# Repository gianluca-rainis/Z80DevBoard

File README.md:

# Z80DevBoard

The Z80DevBoard is an advanced development board for the Z80 microprocessor, based on the RP2040.

This board is meant to be a practical educational tool, to help students learn how the Z80, one of the first CPUs and the foundation of all modern ones, works, and how to develop software for it.

To the Z80 is combined a modern RP2040, a powerful microcontroller designed by Raspberry Pi.
It allows easy interaction with the board's components: you can load a program for the Z80 into RAM; or establish a serial connection with the computer to perform live operations, such as reading and writing to RAM.

The most educational components of the board are the LED matrices, which provide real-time visual feedback on the Z80's activity.
Thanks to these LEDs, you can see which address of the RAM the Z80 is accessing, the byte it's reading or writing, whether it is answering to a BUSREQ with a BUSACK, and essentially all the operations the Z80 is executing.

The board mounts five buttons: the four on the right allow the student to save a Z80 program to flash, load a custom firmware for the RP2040, reset the Z80, and put the Z80 into a wait state.
The button on the left sends a manual clock signal to the Z80, in fact, the board mounts a *Z84C00* (the *CMOS* version of the Z80) specifically to allow it to work even with a manual clock.

The board can be connected to a computer through a *USB-C* port, which provides both power and data transmission.
On the bottom-right of the board, are mounted two pin sockets, to support expansion boards or to be used in more advanced projects that require additional hardware.

For more advanced debugging, when testing custom firmware, the *SWD* and *SWCLK* pins of the RP2040 are accessible on the top-right of the board.

---

## Author
The author of the whole project is: 
**Gianluca Rainis** - [gianluca-rainis](https://github.com/gianluca-rainis) on GitHub.

## Sponsor
The PCB prototyping for this project is sponsored by **[PCBWay](https://www.pcbway.com)**.

The *boards* were manufactured with **high precision**, faithfully **following the PCB design down to the smallest details**.
The *silkscreen* is **crisp and perfectly readable**, with **no errors or misalignments**.
The *board edges* and corner's holes were **cut cleanly and accurately**.
The *drill holes* **match the component footprints exactly**, making placement and soldering straightforward.
The *SMD pads* are **precise and clean**, even for the most challenging footprints, and solder beautifully.

The *PCBWay website* is **intuitive, even for first-time users**.
**Placing an order is simple**, and before proceeding to payment **the design is reviewed by their technical staff**, who catch and communicate **any potential manufacturing issues** promptly and professionally, avoiding problems before production even begins.

> If you are looking for a reliable, high-quality PCB manufacturer for your own projects, **[PCBWay](https://www.pcbway.com)** is highly recommended!

## License
### Hardware design files (schematics, PCB, BOM):
Licensed under [CERN-OHL-S v2.0](LICENSE-CERN-OHL-S.md)

### Software, firmware and documentation:
Licensed under the [MIT License](LICENSE-MIT.md)

## AI Disclaimer
**No AI was used in the conception, design, engineering, or development of this project**.
Every circuit and every design decision is the original work of the author.

*AI tools* were used solely as a **writing assistant** for **parts of the documentation**, to help refine and organize technical explanations.
**All content has been reviewed, verified, and edited by the author.**

## Documentation
The full documentation is available in the [`docs/`](docs/index.md) folder.

## Development Tools
- **PCB Design:** KiCad
- **Documentation and code:** Visual Studio Code

## PCB Manufacturing
The Gerber files for PCB manufacturing are available in the [`gerber/`](gerber/) directory.

## Project Structure
```
Z80DevBoard/
├── customFootprints.pretty/  # Custom footprints
├── docs/                     # The documentation and the guides
├── firmware/                 # The RP2040 firmware
├── gerber/                   # PCB manufacturing files (Gerber format)
├── images/                   # Documentation images and KiCad symbols
├── .gitattributes            # Gitattributes file
├── .gitignore                # Gitignore file
├── gerber.zip                # Zip folder with all the gerber files
├── Z80DevBoard.kicad_pcb     # PCB layout file
├── Z80DevBoard.kicad_pro     # KiCad project file
├── Z80DevBoard.kicad_sch     # Schematic file
├── Z80DevBoard.step          # 3D model
├── BOM.csv                   # Bill Of Materials
├── CHANGELOG.md              # Change log of the project
├── JOURNAL.md                # Journal of the project
├── LICENSE-CERN-OHL-S.md     # CERN-OHL-S License
├── LICENSE-MIT.md            # MIT License
└── README.md                 # This file
```

## Images
### Schematic Diagrams
#### Complete Schematic (A2 format)

#### Z80 Section

#### RP2040 Section

### PCB Layout
#### Without Silkscreen

#### With Silkscreen

### 3D Renders
#### Front View

#### Back View

## Technical Details
- **Size**: 219mm x 108.5mm
- **Layers**: 4
- **Supply Voltage**: 5V, 3v3

## Components Table
|Name|Quantity|Class|Type|
|--|--|--|--|
|Z84C00|1|Microprocessor|Through Holes|
|RP2040|1|Microprocessor|SMD|
|||||
|HM62256BLP|2|Memory|Through Holes|
|W25Q32JVSS|1|Memory|SMD|
|||||
|AMS1117-3.3|1|Power Management|SMD|
|||||
|USB C 2.0 port|1|Data Bus|Through Holes|
|74HC595|3|Data Bus|Through Holes|
|74HC155|1|Data Bus|Through Holes|
|74HCT574|4|Data Bus|Through Holes|
|SN74LVC245APW|3|Data Bus|SMD|
|TXS0104EPW|1|Data Bus|SMD|
|Connector 2 pins|1|Data Bus|Through Holes|
|Connector 2×20 pins|1|Data Bus|Through Holes|
|Connector 2×10 pins|1|Data Bus|Through Holes|
|||||
|Crystal 12MHz 20pF|1|Clock|Through Holes|
|Oscillator 8MHz|1|Clock|SMD|
|||||
|74HC14|1|Support components|Through Holes|
|74HC04|1|Support components|Through Holes|
|74HC00|1|Support components|Through Holes|
|||||
|Resistor 0 ohm|1|Resistor|Through Holes|
|Resistor 27.4 ohm|2|Resistor|Through Holes|
|Resistor 1k ohm|36|Resistor|Through Holes|
|Resistor 3.3k ohm|6|Resistor|Through Holes|
|Resistor 5k ohm|2|Resistor|Through Holes|
|Resistor 10k ohm|13|Resistor|Through Holes|
|Resistor 470k ohm|1|Resistor|Through Holes|
|||||
|Capacitors 15pF|2|Capacitor|Through Holes|
|Capacitors 0.1uF|13|Capacitor|Through Holes|
|Capacitors 1uF|4|Capacitor|Through Holes|
|Capacitors 10uF|2|Capacitor|Through Holes|
|||||
|Button|5|Other|Through Holes|
|Switch|1|Other|Through Holes|
|LED|40|Other|SMD|
|Diodes|24|Other|SMD|
|Fuse 500mA|1|Other|SMD|

## Firmware
### Firmware Video Presentation
https://github.com/user-attachments/assets/ee6d8d69-4003-4e21-8f2b-2f08ad0c8d81

### Build
From the project root, make sure CMake and the ARM GNU toolchain (arm-none-eabi-gcc) are installed.

If the toolchain is not in your PATH, provide it explicitly with PICO_TOOLCHAIN_PATH:

```bash
cmake -S firmware -B firmware/build -DPICO_TOOLCHAIN_PATH=/path/to/arm-gnu-toolchain
cmake --build firmware/build --parallel
```

If the toolchain is already in your PATH, you can omit PICO_TOOLCHAIN_PATH.

#### Output file
The file to load in the RP2040's memory after the build is `Z80DevBoard.uf2`.
You can find it in the `/firmware/build` folder.

> You can find more informations about the firmware, including how to write a custom one, in the [documentation](docs/index.md).

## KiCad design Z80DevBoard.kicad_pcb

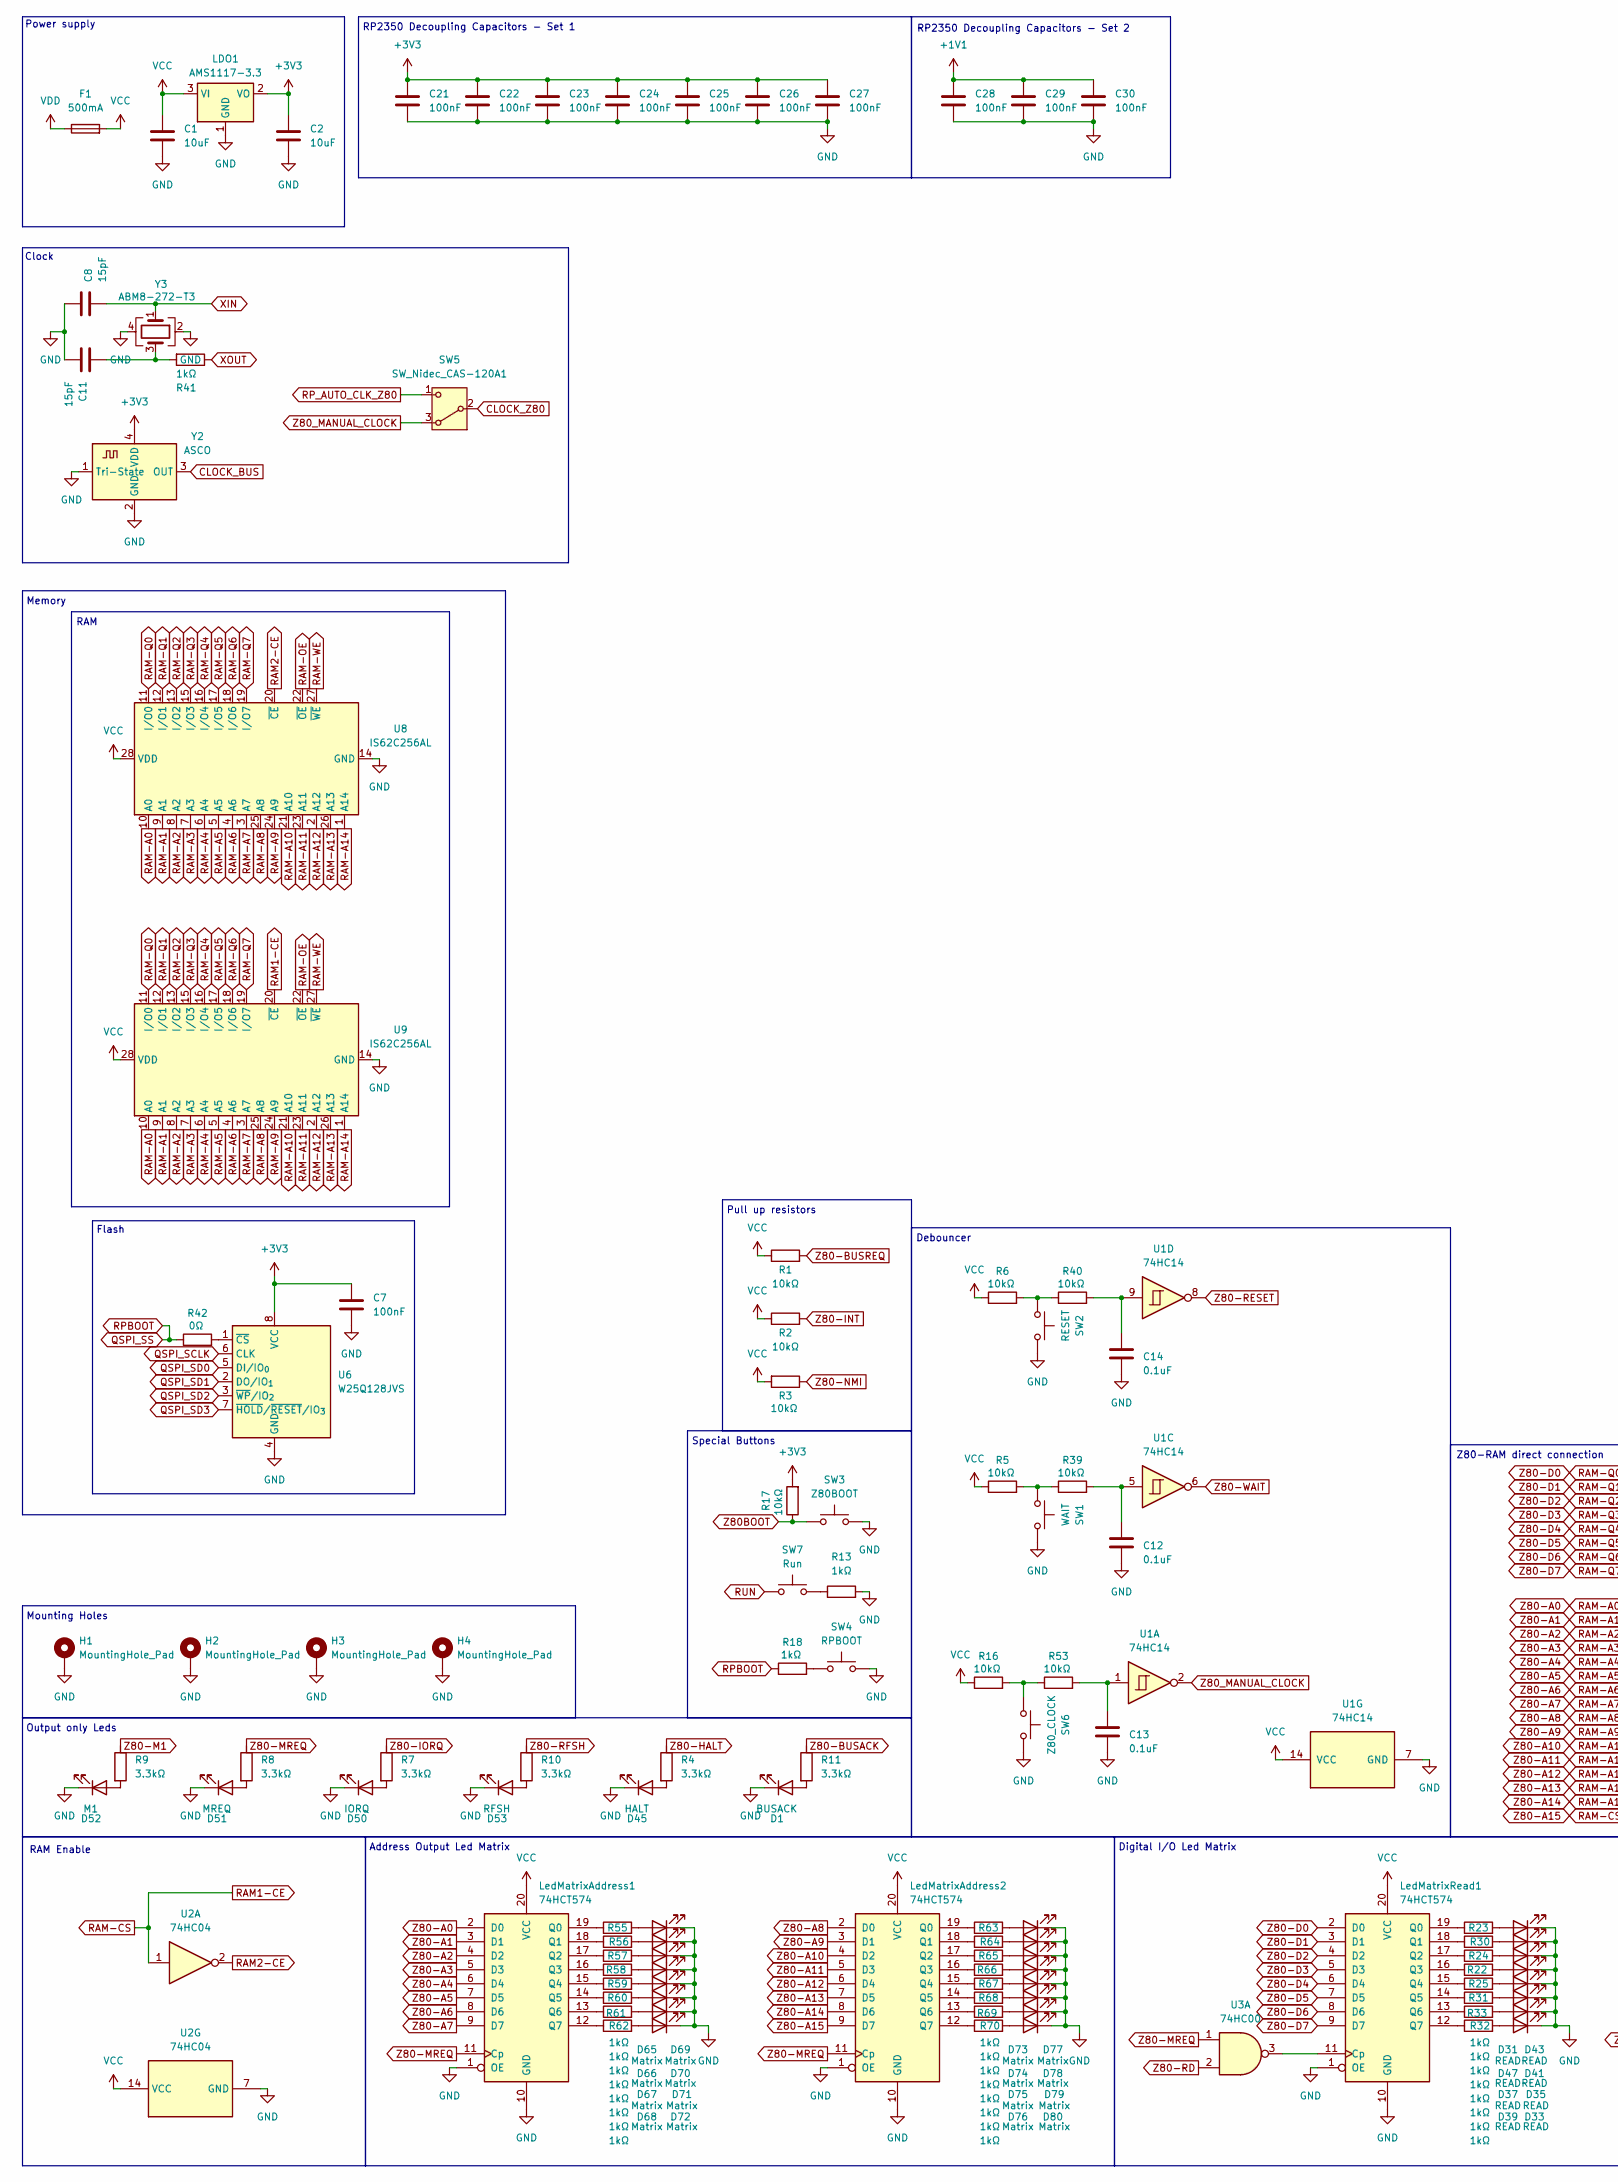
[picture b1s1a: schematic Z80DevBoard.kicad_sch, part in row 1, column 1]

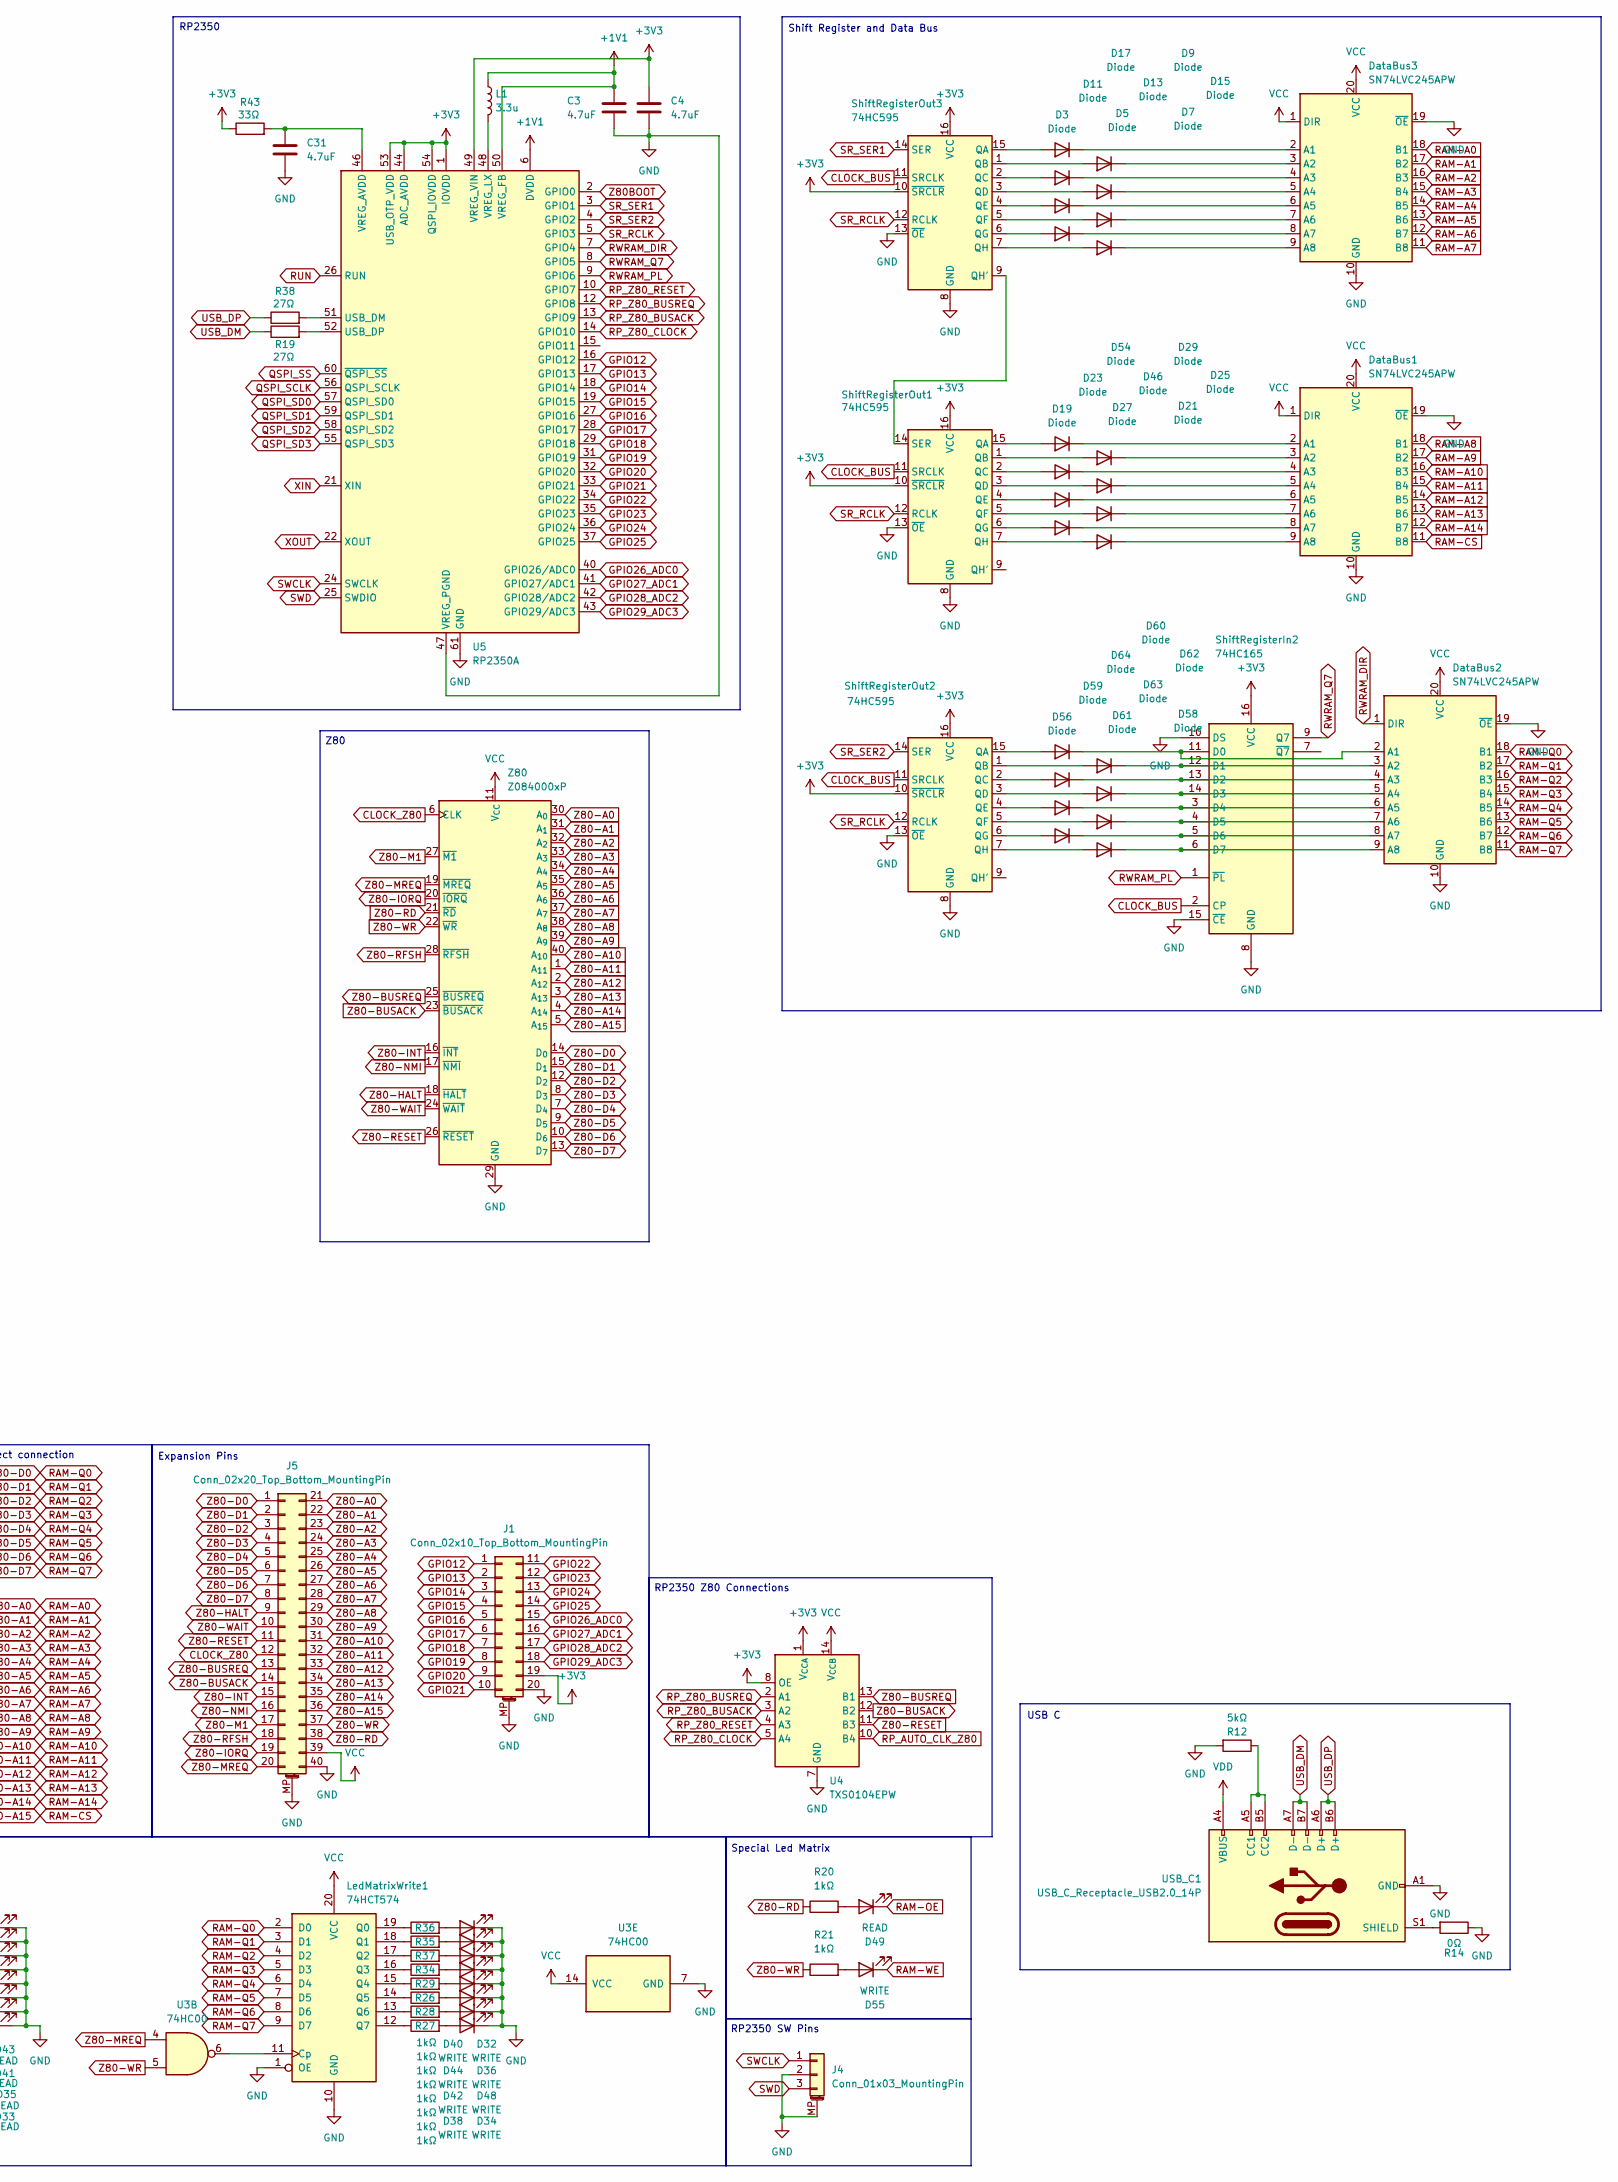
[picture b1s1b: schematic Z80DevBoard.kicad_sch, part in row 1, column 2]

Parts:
C1, C2: 10uF; C_0402_1005Metric
C3, C4, C31: 4.7uF; C_0402_1005Metric
C7, C21, C22, C23, C24, C25, C26, C27, C28, C29, C30: 100nF; C_0402_1005Metric
C8, C11: 15pF; C_0402_1005Metric
C12, C13, C14: 0.1uF; C_0402_1005Metric
D1: BUSACK; LED_PLCC_2835
D3, D5, D7, D9, D11, D13, D15, D17, D19, D21, D23, D25, D27, D29, D46, D54, D56, D58, D59, D60, D61, D62, D63, D64: Diode; D_SOD-523
D31, D33, D35, D37, D39, D41, D43, D47, D49: READ; LED_PLCC_2835
D32, D34, D36, D38, D40, D42, D44, D48, D55: WRITE; LED_PLCC_2835
D45: HALT; LED_PLCC_2835
D50: IORQ; LED_PLCC_2835
D51: MREQ; LED_PLCC_2835
D52: M1; LED_PLCC_2835
D53: RFSH; LED_PLCC_2835
D65, D66, D67, D68, D69, D70, D71, D72, D73, D74, D75, D76, D77, D78, D79, D80: Matrix; LED_PLCC_2835
DataBus1, DataBus2, DataBus3: SN74LVC245APW; TSSOP-20_4.4x6.5mm_P0.65mm
F1: 500mA; Fuse_1206_3216Metric
H1, H2, H3, H4: MountingHole_Pad; MountingHole_4.3mm_M4_Pad_Via
J1: Conn_02x10_Top_Bottom_MountingPin; PinHeader_2x10_P2.54mm_Vertical
J4: Conn_01x03_MountingPin; PinHeader_1x03_P2.54mm_Vertical
J5: Conn_02x20_Top_Bottom_MountingPin; PinHeader_2x20_P2.54mm_Vertical
L1: 3.3u; Inductor
LDO1: AMS1117-3.3; SOT-223-3_TabPin2
LedMatrixAddress1, LedMatrixAddress2: 74HCT574; SO-20_5.3x12.6mm_P1.27mm
LedMatrixRead1: 74HCT574; SO-20_5.3x12.6mm_P1.27mm
LedMatrixWrite1: 74HCT574; SO-20_5.3x12.6mm_P1.27mm
R1, R2, R3, R5, R6, R16, R17, R39, R40, R53: 10kΩ; R_0603_1608Metric
R4, R7, R8, R9, R10, R11: 3.3kΩ; R_0603_1608Metric
R12: 5kΩ; R_0603_1608Metric
R13, R18, R20, R21, R22, R23, R24, R25, R26, R27, R28, R29, R30, R31, R32, R33, R34, R35, R36, R37, R41, R55, R56, R57, R58, R59, R60, R61, R62, R63, R64, R65, R66, R67, R68, R69, R70: 1kΩ; R_0603_1608Metric
R14, R42: 0Ω; R_0603_1608Metric
R19, R38: 27Ω; R_0603_1608Metric
R43: 33Ω; R_0603_1608Metric
SW1: WAIT; SW_SPST_EVQP2_MiddlePushTravel_H2.5mm
SW2: RESET; SW_SPST_EVQP2_MiddlePushTravel_H2.5mm
SW3: Z80BOOT; SW_SPST_EVQP2_MiddlePushTravel_H2.5mm
SW4: RPBOOT; SW_SPST_EVQP2_MiddlePushTravel_H2.5mm
SW5: SW_Nidec_CAS-120A1; SW_Slide-03_Wuerth-WS-SLTV
SW6: Z80_CLOCK; SW_PUSH_6mm_H7.3mm
SW7: Run; SW_SPST_EVQP2_MiddlePushTravel_H2.5mm
ShiftRegisterIn2: 74HC165; SO-16_3.9x9.9mm_P1.27mm
ShiftRegisterOut1, ShiftRegisterOut2, ShiftRegisterOut3: 74HC595; SO-16_3.9x9.9mm_P1.27mm
U1: 74HC14; SO-14_3.9x8.65mm_P1.27mm
U2: 74HC04; SO-14_3.9x8.65mm_P1.27mm
U3: 74HC00; SO-14_3.9x8.65mm_P1.27mm
U4: TXS0104EPW; TSSOP-14_4.4x5mm_P0.65mm
U5: RP2350A; QFN-60-1EP_7x7mm_P0.4mm_EP3.4x3.4mm
U6: W25Q128JVS; SOIC-8_5.3x5.3mm_P1.27mm
U8, U9: IS62C256AL; SOP-28_8.4x18.16mm_P1.27mm
USB_C1: USB_C_Receptacle_USB2.0_14P; USB_C_Receptacle_HRO_TYPE-C-31-M-12
Y2: ASCO; Oscillator_SMD_SiT_PQFN-4Pin_5.0x3.2mm
Y3: ABM8-272-T3; Crystal_SMD_3225-4Pin_3.2x2.5mm; LCSC Part # C20625731
Z80: Z084000xP; DIP-40_W15.24mm

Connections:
+1V1: C3.1, C28.1, C29.1, C30.1, L1.1, U5.6 (DVDD), U5.23 (DVDD), U5.39 (DVDD), U5.50 (VREG_FB)
+3V3: C2.2, C4.1, C7.2, C21.1, C22.1, C23.1, C24.1, C25.1, C26.1, C27.1, J1.19, LDO1.2 (VO), R17.2, R43.1, ShiftRegisterIn2.16 (VCC), ShiftRegisterOut1.10 (~SRCLR), ShiftRegisterOut1.16 (VCC), ShiftRegisterOut2.10 (~SRCLR), ShiftRegisterOut2.16 (VCC), ShiftRegisterOut3.10 (~SRCLR), ShiftRegisterOut3.16 (VCC), U4.1 (V_{CCA}), U4.8 (OE), U5.1 (IOVDD), U5.11 (IOVDD), U5.20 (IOVDD), U5.30 (IOVDD), U5.38 (IOVDD), U5.44 (ADC_AVDD), U5.45 (IOVDD), U5.49 (VREG_VIN), U5.53 (USB_OTP_VDD), U5.54 (QSPI_IOVDD), U6.8 (VCC), Y2.4 (VDD)
CLOCK_BUS: ShiftRegisterIn2.2 (CP), ShiftRegisterOut1.11 (SRCLK), ShiftRegisterOut2.11 (SRCLK), ShiftRegisterOut3.11 (SRCLK), Y2.3 (OUT)
CLOCK_Z80: J5.12, SW5.2 (B), Z80.6 (CLK)
GND: C1.1, C2.1, C3.2, C4.2, C7.1, C8.2, C11.1, C12.1, C13.1, C14.1, C21.2, C22.2, C23.2, C24.2, C25.2, C26.2, C27.2, C28.2, C29.2, C30.2, C31.2, D1.1 (K), D31.1 (K), D32.1 (K), D33.1 (K), D34.1 (K), D35.1 (K), D36.1 (K), D37.1 (K), D38.1 (K), D39.1 (K), D40.1 (K), D41.1 (K), D42.1 (K), D43.1 (K), D44.1 (K), D45.1 (K), D47.1 (K), D48.1 (K), D50.1 (K), D51.1 (K), D52.1 (K), D53.1 (K), D65.1 (K), D66.1 (K), D67.1 (K), D68.1 (K), D69.1 (K), D70.1 (K), D71.1 (K), D72.1 (K), D73.1 (K), D74.1 (K), D75.1 (K), D76.1 (K), D77.1 (K), D78.1 (K), D79.1 (K), D80.1 (K), DataBus1.10 (GND), DataBus1.19 (~OE), DataBus2.10 (GND), DataBus2.19 (~OE), DataBus3.10 (GND), DataBus3.19 (~OE), H1.1 (1_1), H2.1 (1_1), H3.1 (1_1), H4.1 (1_1), J1.20, J1.MP (MountPin), J4.2, J4.MP (MountPin), J5.40, J5.MP (MountPin), LDO1.1 (GND), LedMatrixAddress1.1 (OE), LedMatrixAddress1.10 (GND), LedMatrixAddress2.1 (OE), LedMatrixAddress2.10 (GND), LedMatrixRead1.1 (OE), LedMatrixRead1.10 (GND), LedMatrixWrite1.1 (OE), LedMatrixWrite1.10 (GND), R12.2, R13.2, R14.1, SW1.1, SW2.1, SW3.1, SW4.1, SW6.1, ShiftRegisterIn2.8 (GND), ShiftRegisterIn2.10 (DS), ShiftRegisterIn2.15 (~CE), ShiftRegisterOut1.8 (GND), ShiftRegisterOut1.13 (~OE), ShiftRegisterOut2.8 (GND), ShiftRegisterOut2.13 (~OE), ShiftRegisterOut3.8 (GND), ShiftRegisterOut3.13 (~OE), U1.7 (GND), U2.7 (GND), U3.7 (GND), U4.7 (GND), U5.47 (VREG_PGND), U5.61 (GND), U6.4 (GND), U8.14 (GND), U9.14 (GND), USB_C1.A1 (GND), USB_C1.A12 (GND), USB_C1.B1 (GND), USB_C1.B12 (GND), Y2.1 (Tri-State), Y2.2 (GND), Y3.2, Y3.4, Z80.29 (GND)
GPIO12: J1.1, U5.16 (GPIO12)
GPIO13: J1.2, U5.17 (GPIO13)
GPIO14: J1.3, U5.18 (GPIO14)
GPIO15: J1.4, U5.19 (GPIO15)
GPIO16: J1.5, U5.27 (GPIO16)
GPIO17: J1.6, U5.28 (GPIO17)
GPIO18: J1.7, U5.29 (GPIO18)
GPIO19: J1.8, U5.31 (GPIO19)
GPIO20: J1.9, U5.32 (GPIO20)
GPIO21: J1.10, U5.33 (GPIO21)
GPIO22: J1.11, U5.34 (GPIO22)
GPIO23: J1.12, U5.35 (GPIO23)
GPIO24: J1.13, U5.36 (GPIO24)
GPIO25: J1.14, U5.37 (GPIO25)
GPIO26_ADC0: J1.15, U5.40 (GPIO26/ADC0)
GPIO27_ADC1: J1.16, U5.41 (GPIO27/ADC1)
GPIO28_ADC2: J1.17, U5.42 (GPIO28/ADC2)
GPIO29_ADC3: J1.18, U5.43 (GPIO29/ADC3)
unnamed: C11.2, R41.2, Y3.3
unnamed: C12.2, R39.2, U1.5
unnamed: C13.2, R53.2, U1.1
unnamed: C14.2, R40.2, U1.9
unnamed: D1.2 (A), R11.2
unnamed: D3.2 (A), ShiftRegisterOut3.15 (QA)
unnamed: D3.1 (K), DataBus3.2 (A1)
unnamed: D5.2 (A), ShiftRegisterOut3.1 (QB)
unnamed: D5.1 (K), DataBus3.3 (A2)
unnamed: D7.2 (A), ShiftRegisterOut3.2 (QC)
unnamed: D7.1 (K), DataBus3.4 (A3)
unnamed: D9.2 (A), ShiftRegisterOut3.3 (QD)
unnamed: D9.1 (K), DataBus3.5 (A4)
unnamed: D11.2 (A), ShiftRegisterOut3.4 (QE)
unnamed: D11.1 (K), DataBus3.6 (A5)
unnamed: D13.2 (A), ShiftRegisterOut3.5 (QF)
unnamed: D13.1 (K), DataBus3.7 (A6)
unnamed: D15.2 (A), ShiftRegisterOut3.6 (QG)
unnamed: D15.1 (K), DataBus3.8 (A7)
unnamed: D17.2 (A), ShiftRegisterOut3.7 (QH)
unnamed: D17.1 (K), DataBus3.9 (A8)
unnamed: D19.2 (A), ShiftRegisterOut1.15 (QA)
unnamed: D19.1 (K), DataBus1.2 (A1)
unnamed: D21.2 (A), ShiftRegisterOut1.2 (QC)
unnamed: D21.1 (K), DataBus1.4 (A3)
unnamed: D23.2 (A), ShiftRegisterOut1.4 (QE)
unnamed: D23.1 (K), DataBus1.6 (A5)
unnamed: D25.2 (A), ShiftRegisterOut1.6 (QG)
unnamed: D25.1 (K), DataBus1.8 (A7)
unnamed: D27.2 (A), ShiftRegisterOut1.1 (QB)
unnamed: D27.1 (K), DataBus1.3 (A2)
unnamed: D29.2 (A), ShiftRegisterOut1.3 (QD)
unnamed: D29.1 (K), DataBus1.5 (A4)
unnamed: D31.2 (A), R23.2
unnamed: D32.2 (A), R29.2
unnamed: D33.2 (A), R32.2
unnamed: D34.2 (A), R27.2
unnamed: D35.2 (A), R33.2
unnamed: D36.2 (A), R26.2
unnamed: D37.2 (A), R24.2
unnamed: D38.2 (A), R34.2
unnamed: D39.2 (A), R22.2
unnamed: D40.2 (A), R36.2
unnamed: D41.2 (A), R31.2
unnamed: D42.2 (A), R37.2
unnamed: D43.2 (A), R25.2
unnamed: D44.2 (A), R35.2
unnamed: D45.2 (A), R4.2
unnamed: D46.2 (A), ShiftRegisterOut1.5 (QF)
unnamed: D46.1 (K), DataBus1.7 (A6)
unnamed: D47.2 (A), R30.2
unnamed: D48.2 (A), R28.2
unnamed: D49.2 (A), R20.2
unnamed: D50.2 (A), R7.2
unnamed: D51.2 (A), R8.2
unnamed: D52.2 (A), R9.2
unnamed: D53.2 (A), R10.2
unnamed: D54.2 (A), ShiftRegisterOut1.7 (QH)
unnamed: D54.1 (K), DataBus1.9 (A8)
unnamed: D55.2 (A), R21.2
unnamed: D56.2 (A), ShiftRegisterOut2.15 (QA)
unnamed: D56.1 (K), DataBus2.2 (A1), ShiftRegisterIn2.11 (D0)
unnamed: D58.2 (A), ShiftRegisterOut2.2 (QC)
unnamed: D58.1 (K), DataBus2.4 (A3), ShiftRegisterIn2.13 (D2)
unnamed: D59.2 (A), ShiftRegisterOut2.4 (QE)
unnamed: D59.1 (K), DataBus2.6 (A5), ShiftRegisterIn2.3 (D4)
unnamed: D60.2 (A), ShiftRegisterOut2.6 (QG)
unnamed: D60.1 (K), DataBus2.8 (A7), ShiftRegisterIn2.5 (D6)
unnamed: D61.2 (A), ShiftRegisterOut2.1 (QB)
unnamed: D61.1 (K), DataBus2.3 (A2), ShiftRegisterIn2.12 (D1)
unnamed: D62.2 (A), ShiftRegisterOut2.3 (QD)
unnamed: D62.1 (K), DataBus2.5 (A4), ShiftRegisterIn2.14 (D3)
unnamed: D63.2 (A), ShiftRegisterOut2.5 (QF)
unnamed: D63.1 (K), DataBus2.7 (A6), ShiftRegisterIn2.4 (D5)
unnamed: D64.2 (A), ShiftRegisterOut2.7 (QH)
unnamed: D64.1 (K), DataBus2.9 (A8), ShiftRegisterIn2.6 (D7)
unnamed: D65.2 (A), R55.2
unnamed: D66.2 (A), R56.2
unnamed: D67.2 (A), R57.2
unnamed: D68.2 (A), R58.2
unnamed: D69.2 (A), R59.2
unnamed: D70.2 (A), R60.2
unnamed: D71.2 (A), R61.2
unnamed: D72.2 (A), R62.2
unnamed: D73.2 (A), R63.2
unnamed: D74.2 (A), R64.2
unnamed: D75.2 (A), R65.2
unnamed: D76.2 (A), R66.2
unnamed: D77.2 (A), R67.2
unnamed: D78.2 (A), R68.2
unnamed: D79.2 (A), R69.2
unnamed: D80.2 (A), R70.2
unnamed: LedMatrixAddress1.19 (Q0), R55.1
unnamed: LedMatrixAddress1.18 (Q1), R56.1
unnamed: LedMatrixAddress1.17 (Q2), R57.1
unnamed: LedMatrixAddress1.16 (Q3), R58.1
unnamed: LedMatrixAddress1.15 (Q4), R59.1
unnamed: LedMatrixAddress1.14 (Q5), R60.1
unnamed: LedMatrixAddress1.13 (Q6), R61.1
unnamed: LedMatrixAddress1.12 (Q7), R62.1
unnamed: LedMatrixAddress2.19 (Q0), R63.1
unnamed: LedMatrixAddress2.18 (Q1), R64.1
unnamed: LedMatrixAddress2.17 (Q2), R65.1
unnamed: LedMatrixAddress2.16 (Q3), R66.1
unnamed: LedMatrixAddress2.15 (Q4), R67.1
unnamed: LedMatrixAddress2.14 (Q5), R68.1
unnamed: LedMatrixAddress2.13 (Q6), R69.1
unnamed: LedMatrixAddress2.12 (Q7), R70.1
unnamed: LedMatrixRead1.11 (Cp), U3.3
unnamed: LedMatrixRead1.19 (Q0), R23.1
unnamed: LedMatrixRead1.18 (Q1), R30.1
unnamed: LedMatrixRead1.17 (Q2), R24.1
unnamed: LedMatrixRead1.16 (Q3), R22.1
unnamed: LedMatrixRead1.15 (Q4), R25.1
unnamed: LedMatrixRead1.14 (Q5), R31.1
unnamed: LedMatrixRead1.13 (Q6), R33.1
unnamed: LedMatrixRead1.12 (Q7), R32.1
unnamed: LedMatrixWrite1.11 (Cp), U3.6
unnamed: LedMatrixWrite1.19 (Q0), R36.1
unnamed: LedMatrixWrite1.18 (Q1), R35.1
unnamed: LedMatrixWrite1.17 (Q2), R37.1
unnamed: LedMatrixWrite1.16 (Q3), R34.1
unnamed: LedMatrixWrite1.15 (Q4), R29.1
unnamed: LedMatrixWrite1.14 (Q5), R26.1
unnamed: LedMatrixWrite1.13 (Q6), R28.1
unnamed: LedMatrixWrite1.12 (Q7), R27.1
unnamed: R13.1, SW7.2
unnamed: R16.2, R53.1, SW6.2
unnamed: R18.2, SW4.2
unnamed: R5.2, R39.1, SW1.2
unnamed: R6.2, R40.1, SW2.2
unnamed: ShiftRegisterOut1.14 (SER), ShiftRegisterOut3.9 (QH')
unnamed: R38.2, U5.51 (USB_DM)
unnamed: R19.2, U5.52 (USB_DP)
unnamed: C31.1, R43.2, U5.46 (VREG_AVDD)
unnamed: L1.2, U5.48 (VREG_LX)
unnamed: R42.2, U6.1 (~CS)
unnamed: R12.1, USB_C1.A5 (CC1), USB_C1.B5 (CC2)
unnamed: R14.2, USB_C1.S1 (SHIELD)
QSPI_SCLK: U5.56 (QSPI_SCLK), U6.6 (CLK)
QSPI_SD0: U5.57 (QSPI_SD0), U6.5 (DI/IO_{0})
QSPI_SD1: U5.59 (QSPI_SD1), U6.2 (DO/IO_{1})
QSPI_SD2: U5.58 (QSPI_SD2), U6.3 (~WP/IO_{2})
QSPI_SD3: U5.55 (QSPI_SD3), U6.7 (~HOLD/~RESET/IO_{3})
QSPI_SS: R18.1, R42.1, U5.60 (~QSPI_SS)
RAM2-CE: U2.2, U8.20 (~CE)
RAM-A0: DataBus3.18 (B1), J5.21, LedMatrixAddress1.2 (D0), U8.10 (A0), U9.10 (A0), Z80.30 (A_{0})
RAM-A1: DataBus3.17 (B2), J5.22, LedMatrixAddress1.3 (D1), U8.9 (A1), U9.9 (A1), Z80.31 (A_{1})
RAM-A2: DataBus3.16 (B3), J5.23, LedMatrixAddress1.4 (D2), U8.8 (A2), U9.8 (A2), Z80.32 (A_{2})
RAM-A3: DataBus3.15 (B4), J5.24, LedMatrixAddress1.5 (D3), U8.7 (A3), U9.7 (A3), Z80.33 (A_{3})
RAM-A4: DataBus3.14 (B5), J5.25, LedMatrixAddress1.6 (D4), U8.6 (A4), U9.6 (A4), Z80.34 (A_{4})
RAM-A5: DataBus3.13 (B6), J5.26, LedMatrixAddress1.7 (D5), U8.5 (A5), U9.5 (A5), Z80.35 (A_{5})
RAM-A6: DataBus3.12 (B7), J5.27, LedMatrixAddress1.8 (D6), U8.4 (A6), U9.4 (A6), Z80.36 (A_{6})
RAM-A7: DataBus3.11 (B8), J5.28, LedMatrixAddress1.9 (D7), U8.3 (A7), U9.3 (A7), Z80.37 (A_{7})
RAM-A8: DataBus1.18 (B1), J5.29, LedMatrixAddress2.2 (D0), U8.25 (A8), U9.25 (A8), Z80.38 (A_{8})
RAM-A9: DataBus1.17 (B2), J5.30, LedMatrixAddress2.3 (D1), U8.24 (A9), U9.24 (A9), Z80.39 (A_{9})
RAM-A10: DataBus1.16 (B3), J5.31, LedMatrixAddress2.4 (D2), U8.21 (A10), U9.21 (A10), Z80.40 (A_{10})
RAM-A11: DataBus1.15 (B4), J5.32, LedMatrixAddress2.5 (D3), U8.23 (A11), U9.23 (A11), Z80.1 (A_{11})
RAM-A12: DataBus1.14 (B5), J5.33, LedMatrixAddress2.6 (D4), U8.2 (A12), U9.2 (A12), Z80.2 (A_{12})
RAM-A13: DataBus1.13 (B6), J5.34, LedMatrixAddress2.7 (D5), U8.26 (A13), U9.26 (A13), Z80.3 (A_{13})
RAM-A14: DataBus1.12 (B7), J5.35, LedMatrixAddress2.8 (D6), U8.1 (A14), U9.1 (A14), Z80.4 (A_{14})
RAM-CS: DataBus1.11 (B8), J5.36, LedMatrixAddress2.9 (D7), U2.1, U9.20 (~CE), Z80.5 (A_{15})
RAM-OE: D49.1 (K), U8.22 (~OE), U9.22 (~OE)
RAM-Q0: DataBus2.18 (B1), J5.1, LedMatrixRead1.2 (D0), LedMatrixWrite1.2 (D0), U8.11 (I/O0), U9.11 (I/O0), Z80.14 (D_{0})
RAM-Q1: DataBus2.17 (B2), J5.2, LedMatrixRead1.3 (D1), LedMatrixWrite1.3 (D1), U8.12 (I/O1), U9.12 (I/O1), Z80.15 (D_{1})
RAM-Q2: DataBus2.16 (B3), J5.3, LedMatrixRead1.4 (D2), LedMatrixWrite1.4 (D2), U8.13 (I/O2), U9.13 (I/O2), Z80.12 (D_{2})
RAM-Q3: DataBus2.15 (B4), J5.4, LedMatrixRead1.5 (D3), LedMatrixWrite1.5 (D3), U8.15 (I/O3), U9.15 (I/O3), Z80.8 (D_{3})
RAM-Q4: DataBus2.14 (B5), J5.5, LedMatrixRead1.6 (D4), LedMatrixWrite1.6 (D4), U8.16 (I/O4), U9.16 (I/O4), Z80.7 (D_{4})
RAM-Q5: DataBus2.13 (B6), J5.6, LedMatrixRead1.7 (D5), LedMatrixWrite1.7 (D5), U8.17 (I/O5), U9.17 (I/O5), Z80.9 (D_{5})
RAM-Q6: DataBus2.12 (B7), J5.7, LedMatrixRead1.8 (D6), LedMatrixWrite1.8 (D6), U8.18 (I/O6), U9.18 (I/O6), Z80.10 (D_{6})
RAM-Q7: DataBus2.11 (B8), J5.8, LedMatrixRead1.9 (D7), LedMatrixWrite1.9 (D7), U8.19 (I/O7), U9.19 (I/O7), Z80.13 (D_{7})
RAM-WE: D55.1 (K), U8.27 (~WE), U9.27 (~WE)
RP_AUTO_CLK_Z80: SW5.1 (C), U4.10 (B4)
RP_Z80_BUSACK: U4.3 (A2), U5.13 (GPIO9)
RP_Z80_BUSREQ: U4.2 (A1), U5.12 (GPIO8)
RP_Z80_CLOCK: U4.5 (A4), U5.14 (GPIO10)
RP_Z80_RESET: U4.4 (A3), U5.10 (GPIO7)
RUN: SW7.1, U5.26 (RUN)
RWRAM_DIR: DataBus2.1 (DIR), U5.7 (GPIO4)
RWRAM_PL: ShiftRegisterIn2.1 (~PL), U5.9 (GPIO6)
RWRAM_Q7: ShiftRegisterIn2.9 (Q7), U5.8 (GPIO5)
SR_RCLK: ShiftRegisterOut1.12 (RCLK), ShiftRegisterOut2.12 (RCLK), ShiftRegisterOut3.12 (RCLK), U5.5 (GPIO3)
SR_SER1: ShiftRegisterOut3.14 (SER), U5.3 (GPIO1)
SR_SER2: ShiftRegisterOut2.14 (SER), U5.4 (GPIO2)
SWCLK: J4.1, U5.24 (SWCLK)
SWD: J4.3, U5.25 (SWDIO)
USB_DM: R19.1, USB_C1.A7 (D-), USB_C1.B7 (D-)
USB_DP: R38.1, USB_C1.A6 (D+), USB_C1.B6 (D+)
VCC: C1.2, DataBus1.1 (DIR), DataBus1.20 (VCC), DataBus2.20 (VCC), DataBus3.1 (DIR), DataBus3.20 (VCC), F1.2, J5.39, LDO1.3 (VI), LedMatrixAddress1.20 (VCC), LedMatrixAddress2.20 (VCC), LedMatrixRead1.20 (VCC), LedMatrixWrite1.20 (VCC), R1.1, R2.1, R3.2, R5.1, R6.1, R16.1, U1.14 (VCC), U2.14 (VCC), U3.14 (VCC), U4.14 (V_{CCB}), U8.28 (VDD), U9.28 (VDD), Z80.11 (V_{CC})
VDD: F1.1, USB_C1.A4 (VBUS), USB_C1.A9 (VBUS), USB_C1.B4 (VBUS), USB_C1.B9 (VBUS)
XIN: C8.1, U5.21 (XIN), Y3.1
XOUT: R41.1, U5.22 (XOUT)
Z80-BUSACK: J5.14, R11.1, U4.12 (B2), Z80.23 (~BUSACK)
Z80-BUSREQ: J5.13, R1.2, U4.13 (B1), Z80.25 (~BUSREQ)
Z80-HALT: J5.9, R4.1, Z80.18 (~HALT)
Z80-INT: J5.15, R2.2, Z80.16 (~INT)
Z80-IORQ: J5.19, R7.1, Z80.20 (~IORQ)
Z80-M1: J5.17, R9.1, Z80.27 (~M1)
Z80-MREQ: J5.20, LedMatrixAddress1.11 (Cp), LedMatrixAddress2.11 (Cp), R8.1, U3.1, U3.4, Z80.19 (~MREQ)
Z80-NMI: J5.16, R3.1, Z80.17 (~NMI)
Z80-RD: J5.38, R20.1, U3.2, Z80.21 (~RD)
Z80-RESET: J5.11, U1.8, U4.11 (B3), Z80.26 (~RESET)
Z80-RFSH: J5.18, R10.1, Z80.28 (~RFSH)
Z80-WAIT: J5.10, U1.6, Z80.24 (~WAIT)
Z80-WR: J5.37, R21.1, U3.5, Z80.22 (~WR)
Z80BOOT: R17.1, SW3.2, U5.2 (GPIO0)
Z80_MANUAL_CLOCK: SW5.3 (A), U1.2

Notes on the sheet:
Digital I/O Led Matrix
RAM
Special Buttons
Power supply
RP2350 Z80 Connections
Debouncer
Expansion Pins
Z80
Mounting Holes
Output only Leds
Clock
USB C
Address Output Led Matrix
RP2350 Decoupling Capacitors - Set 1
RP2350 SW Pins
Z80-RAM direct connection
RP2350
Special Led Matrix
Pull up resistors
Shift Register and Data Bus
Memory
Flash
RAM Enable
RP2350 Decoupling Capacitors - Set 2

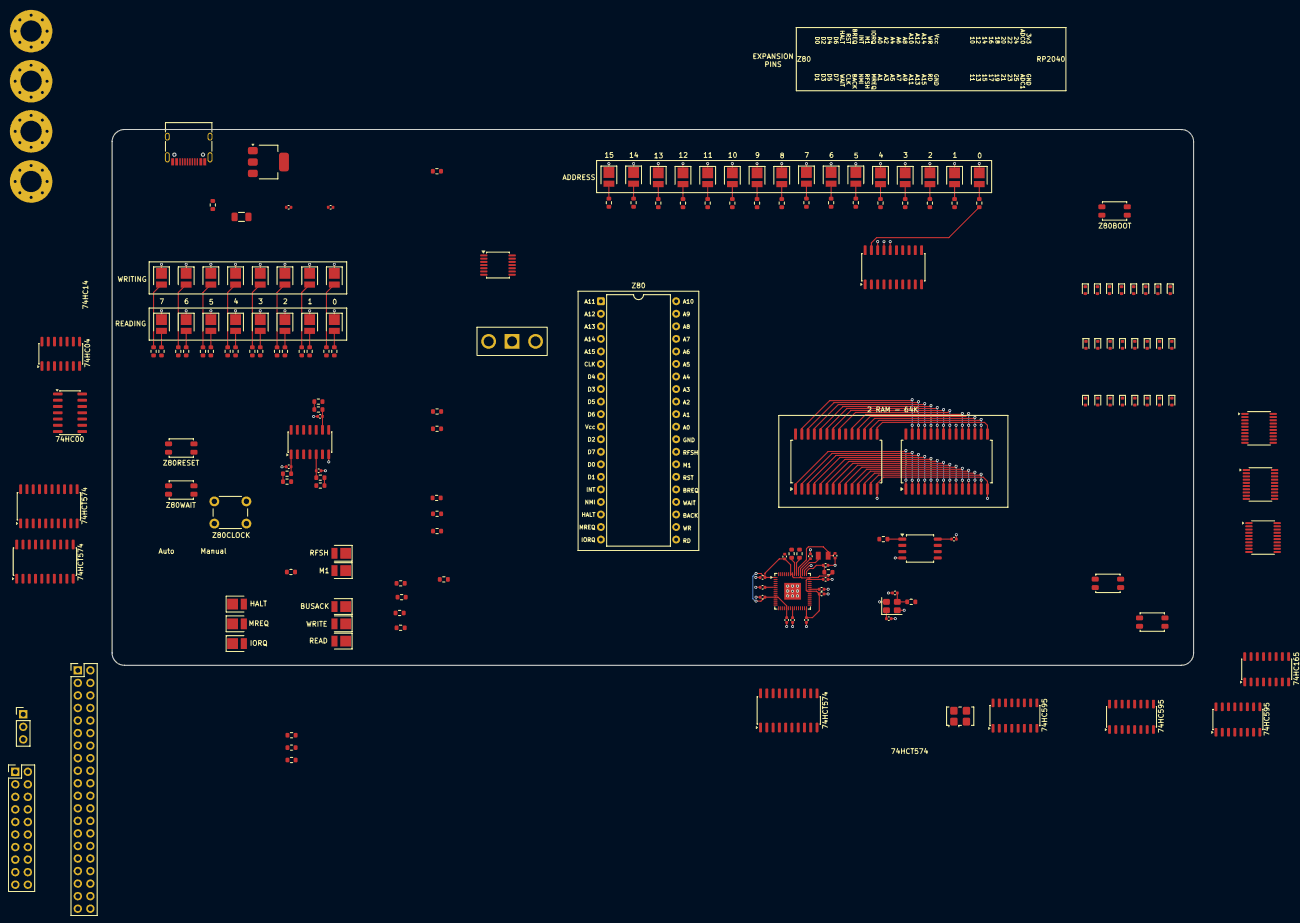
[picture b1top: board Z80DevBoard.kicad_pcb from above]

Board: 2 copper layers, 219.0 x 108.5 mm, 184 parts (0 on the bottom side), 230 nets.

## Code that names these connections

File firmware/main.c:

/* 
 *  RP2040 connections:
 *  GPIO0 - Input 0 save Z80 new program from USB to flash
 *  GPIO1 - Output of the address of the RAM (serial 16 bit)
 *  GPIO2 - Output of the data of the RAM (serial 8 bit)
 *  GPIO3 - Output of the rotation clock of the shift registers
 *  GPIO4 - Output of the direction of the operation to RAM (1 for write, 0 for read)
 *  GPIO5 - Output of the RESET signal to Z80
 *  GPIO6 - Input of the byte of data read from RAM (serial 8 bit)
 *  GPIO7 - Output of the moment when read the RAM (0 for read, 1 for shift)
 *  GPIO8 - DISCONNECTED
 *  GPIO9 - DISCONNECTED
 *  GPIO10 - Output of the BUSREQ signal to Z80
 *  GPIO11 - Input of the BUSACK signal from Z80
 *  GPIO12 - Expansion Pin
 *  GPIO13 - Expansion Pin
 *  GPIO14 - Expansion Pin
 *  GPIO15 - Expansion Pin
 *  GPIO16 - Expansion Pin
 *  GPIO17 - Expansion Pin
 *  GPIO18 - Expansion Pin
 *  GPIO19 - Expansion Pin
 *  GPIO20 - Expansion Pin
 *  GPIO21 - Expansion Pin
 *  GPIO22 - Expansion Pin
 *  GPIO23 - Expansion Pin
 *  GPIO24 - Expansion Pin
 *  GPIO25 - Expansion Pin
 *  GPIO26-ADC0 - Expansion Pin
 *  GPIO27-ADC1 - Expansion Pin
 *  GPIO28-ADC2 - Expansion Pin
 *  GPIO29-ADC3 - Expansion Pin
 */

#include "firmware.h"
#include <stdbool.h>

int main() {
    setup();

    while (true)
    {
        loop();
    }

    return 0;
}

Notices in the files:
README.md:
Hardware License
License: MIT License
